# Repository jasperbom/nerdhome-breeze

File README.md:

# Nerdhome Breeze

Lokale wifi-adapters voor airco's, met ESPHome in Home Assistant. Geen cloud, geen app: het printje gaat op de service- of wifi-aansluiting van de binnenunit en praat rechtstreeks met de airco.

| Variant | Aansluiting | Print | Firmware |
|---|---|---|---|
| **Breeze voor Toshiba** | CN22 (wifi-poort, 5 V, 9600 8E1) | [`toshiba/`](toshiba/README.md), 24 × 34 mm | [`esphome/breeze-toshiba.yaml`](esphome/breeze-toshiba.yaml) |
| **Breeze voor Daikin** | S21 (12–15 V, 2400 8E2) | [`daikin/`](daikin/README.md), 28 × 42 mm | [`esphome/breeze-daikin.yaml`](esphome/breeze-daikin.yaml) |

Beide printjes gebruiken een ESP32-C6-MINI-1U (wifi 6, U.FL-antenne), USB-C voor de eerste keer flashen en MOSFET-niveau-omzetters naar de 5 V-logica van de airco.

**Status:** beide printjes zijn revisie 1.0 en nog niet in hardware getest.

## Firmware

De ESPHome-config staat in [`esphome/`](esphome/) en wordt op twee manieren gebruikt.

**1. Eigen config per binnenunit (voor ESPHome-gebruikers)**
`breeze-<merk>.yaml` bevat alles wat voor elke unit van dat merk gelijk is. Elke unit krijgt in de ESPHome Builder een kleine eigen yaml (voorbeelden: [`toshiba-woonkamer.yaml`](esphome/toshiba-woonkamer.yaml), [`daikin-voorbeeld.yaml`](esphome/daikin-voorbeeld.yaml)) met alleen naam, API-sleutel en wifi. De rest komt via `packages:` van GitHub (`refresh: 1d`).

1. Zet de waarden uit [`esphome/secrets.yaml.example`](esphome/secrets.yaml.example) in de `secrets.yaml` van de ESPHome Builder, met per unit een eigen API-sleutel (`openssl rand -base64 32`).
2. Maak per unit een kopie van het voorbeeld en pas `name`, `friendly_name` en de naam van de API-sleutel aan.
3. Eerste keer via USB-C flashen (deksel eraf, print los van de airco; niet herkend? houd BOOT ingedrukt bij het insteken). Daarna gaan updates via wifi.

**2. Kant-en-klare firmware (voor klanten, zonder compileren)**
GitHub Actions bouwt `breeze-<merk>.factory.yaml` bij elke wijziging in `esphome/` en elke 1e van de maand met de nieuwste ESPHome, en publiceert op GitHub Pages:

- Webinstaller: https://jasperbom.github.io/nerdhome-breeze/ (Chrome/Edge, via USB, wifi meteen instellen via Improv)
- Update-kanalen: `…/firmware/toshiba/manifest.json` en `…/firmware/daikin/manifest.json`

Units met deze firmware krijgen in Home Assistant een update-entiteit *Firmware*; elke nieuwe build verschijnt daar als update. Met *Take control* in de ESPHome Builder stap je over op route 1.

### Wat Breeze voor Toshiba in Home Assistant zet

- Het airco-entity (standen, temperatuur, ventilator, zwenken verticaal én horizontaal) en het vermogensniveau.
- **Actie**: of de unit echt koelt, verwarmt, ontvochtigt, ventileert of stilstaat (*inactief*), op basis van de compressor in het buitendeel.
- **Presets**: Eco, Boost (Hi POWER), Silent 1 en 2, Slapen, Comfort, Fireplace 1 en 2. Vorstbeveiliging (8 °C) en de vloerstand staan bewust uit.
- **Lamellen verticaal**: vaste stand (boven t/m onder) of zwenken.
- **Plasmafilter** aan/uit. Heeft de binnenunit geen plasmafilter, dan meldt hij nooit een stand en blijft de schakelaar op *Onbekend*.
- **Zelfreiniging**: aan zolang de unit zich na koelen of drogen droogblaast (ca. 30 minuten, ventilator laag, airco staat op uit).
- **Wifi-lampje** op de binnenunit aan/uit; de stand wordt onthouden.
- **Ruimtetemperatuur**: de unit meldt hele graden, elke minuut opgevraagd en afgevlakt met een glijdend gemiddelde over 10 minuten.
- **Buitentemperatuur** van de buitenunit (alleen als het buitendeel aan staat).
- **Energie vandaag** (kWh) uit de eigen meter van de unit en een geschat **Vermogen** (W), op modellen met energiemeting. De unit krijgt daarvoor de klok van Home Assistant.
- **Draaiuren** (totaal) en **Draaiuren sinds onderhoud**, met een instelbaar **Onderhoudsinterval** (standaard 250 uur), een melding **Onderhoud nodig** en een knop **Onderhoud uitgevoerd** die de teller op nul zet. Een uur telt mee zodra de unit aan staat, in elke stand.
- **Diagnose, standaard verborgen**: compressorbelasting en -stroom, pers- en zuiggastemperatuur, warmtewisselaar buiten en binnen (TC, TCJ) en ventilatortoerental. Deze komen uit statusberichten die niet elk model stuurt; zet ze in Home Assistant aan als je unit ze levert.
- **Typenummer, serienummer en softwareversie** van binnen- en buitendeel, zoals de unit ze zelf doorgeeft (handig bij support en garantie).
- **Van de Breeze zelf**: chiptemperatuur, IP-adres, wifi-netwerk, wifi-signaal, ESPHome-versie en uptime.

Wat een unit niet ondersteunt (bijvoorbeeld horizontale lamellen of een preset), negeert hij. Losse ESPHome-entiteiten kunnen in Home Assistant niet op *Niet beschikbaar* staan; dat kan alleen het hele apparaat.

## Licenties

De firmware gebruikt de ESPHome-componenten [esphome_toshiba_suzumi](https://github.com/pedobry/esphome_toshiba_suzumi) en [esphome-daikin-s21](https://github.com/asund/esphome-daikin-s21), beide GPL-3. Wie gecompileerde firmware verspreidt, moet de broncode beschikbaar stellen; dat gebeurt hier: de config staat in deze repository en de componenten worden bij het bouwen van GitHub gehaald. De Toshiba-component staat als aangepaste kopie (met plasmafilter) in [`esphome/components/toshiba_suzumi/`](esphome/components/toshiba_suzumi/NERDHOME.md), met de oorspronkelijke GPL-3-licentie en een overzicht van de wijzigingen. Merknamen worden alleen beschrijvend gebruikt ("voor Toshiba", "voor Daikin"); dit product is niet van of goedgekeurd door Toshiba of Daikin.

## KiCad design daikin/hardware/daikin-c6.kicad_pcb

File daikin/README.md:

# Breeze voor Daikin: print `daikin-c6`

Onderdeel van [Nerdhome Breeze](../README.md). Firmware: [`esphome/breeze-daikin.yaml`](../esphome/breeze-daikin.yaml).

Printje van 28 × 42 mm voor de **S21-aansluiting** van Daikin-binnenunits (Emura, Perfera, Stylish, Sensira, Comfora en andere huishoudelijke splitunits). Het zet de unit lokaal via ESPHome in Home Assistant, met het component [esphome-daikin-s21](https://github.com/asund/esphome-daikin-s21) (UART 2400 baud, 8E2). Commerciële systemen met P1/P2 (Sky Air, VRV, Altherma) vallen hier niet onder.

**Status: revisie 1.0, nog niet in hardware getest.** ERC en DRC (met schema-pariteit) zijn schoon en de footprints zijn uitgelijnd tegen JLCPCB's eigen footprints. Test eerst één bordje op één unit.

## Verschil met de Toshiba-print

Zelfde basis: ESP32-C6-MINI-1U met U.FL-antenne, AP2112K 3,3 V-regelaar, Schottky-OR met USB-C, twee AO3400A-niveau-omzetters, BOOT-knop en status-LED, dezelfde GPIO's (19 = TX, 20 = RX, 23 = LED).

| | Toshiba (`toshiba-c6`) | Daikin (`daikin-c6`) |
|---|---|---|
| Aansluiting | CN22, JST PA 2,0 mm | S21, JST EH 2,5 mm (S5B-EH, zijingang) |
| Voeding uit de airco | 5 V | 12–15 V op pin 4 → buck-converter AP63205 → 5 V |
| Pull-ups datalijnen | op de 5 V van de airco | op de eigen 5 V van de buck (Daikin-lijnen zijn open drain) |
| UART | 9600 8E1 | 2400 8E2 |
| Afmeting | 24 × 34 mm | 28 × 42 mm (EH-connector en USB-C passen niet samen op 24 mm) |

## Aansluiting J1 (Daikin S21)

| Pin | Functie | Op de print |
|---|---|---|
| 1 | Vref 5 V (referentie, soms afwezig) | **niet aangesloten** |
| 2 | TX van de airco | ESP RX (GPIO20) via Q2 |
| 3 | RX van de airco | ESP TX (GPIO19) via Q1 |
| 4 | Vcc 12–15 V | voeding via buck U3 |
| 5 | GND | GND |

Kabel: EHR-5 aan beide kanten, pin 1 op pin 1 (1-op-1). Sommige units hebben een JST PAP-aansluiting (2,0 mm) in plaats van EH; dan heb je een PAP-naar-EH-kabel nodig. Meet vóór het insteken pin 4 tegen pin 5: daar hoort 12–15 V te staan.

## Bestellen bij JLCPCB

Zoals bij de Toshiba-print: upload `production/daikin-c6_gerbers_jlcpcb.zip` (2 lagen, 1,6 mm), zet PCB Assembly aan voor de bovenkant en upload `production/daikin-c6_bom_jlcpcb.csv` en `production/daikin-c6_cpl_jlcpcb.csv`. Controleer in de plaatsingsvoorbeeldweergave vooral U3 (buck), U2, Q1/Q2, D1/D2 (streep = kathode), D3 en de richting van J1 (opening naar de onderrand).

Extended parts: U1, U2, U3 (AP63205WU-7), L1 (4,7 µH), J1 (S5B-EH), J2 en SW1.

## Veiligheid

- Sluit nooit USB aan terwijl het bordje aan de airco hangt.
- Werk alleen aan de binnenunit met de stroom eraf.
- Gebruik nooit de S403-aansluiting met pin 10: daar staat ongeveer 327 V DC op.

## Bestanden en opnieuw genereren

Zelfde opbouw als `toshiba/`: `hardware/` (KiCad 9), `production/` (JLCPCB), `docs/` (schema-PDF, assemblagetekening, renders), `tools/` (generatoren; `tools/circuit.py` is de enige bron voor onderdelen en netten, `tools/build_pcb.sh` en `tools/gen_outputs.sh` bouwen alles opnieuw).

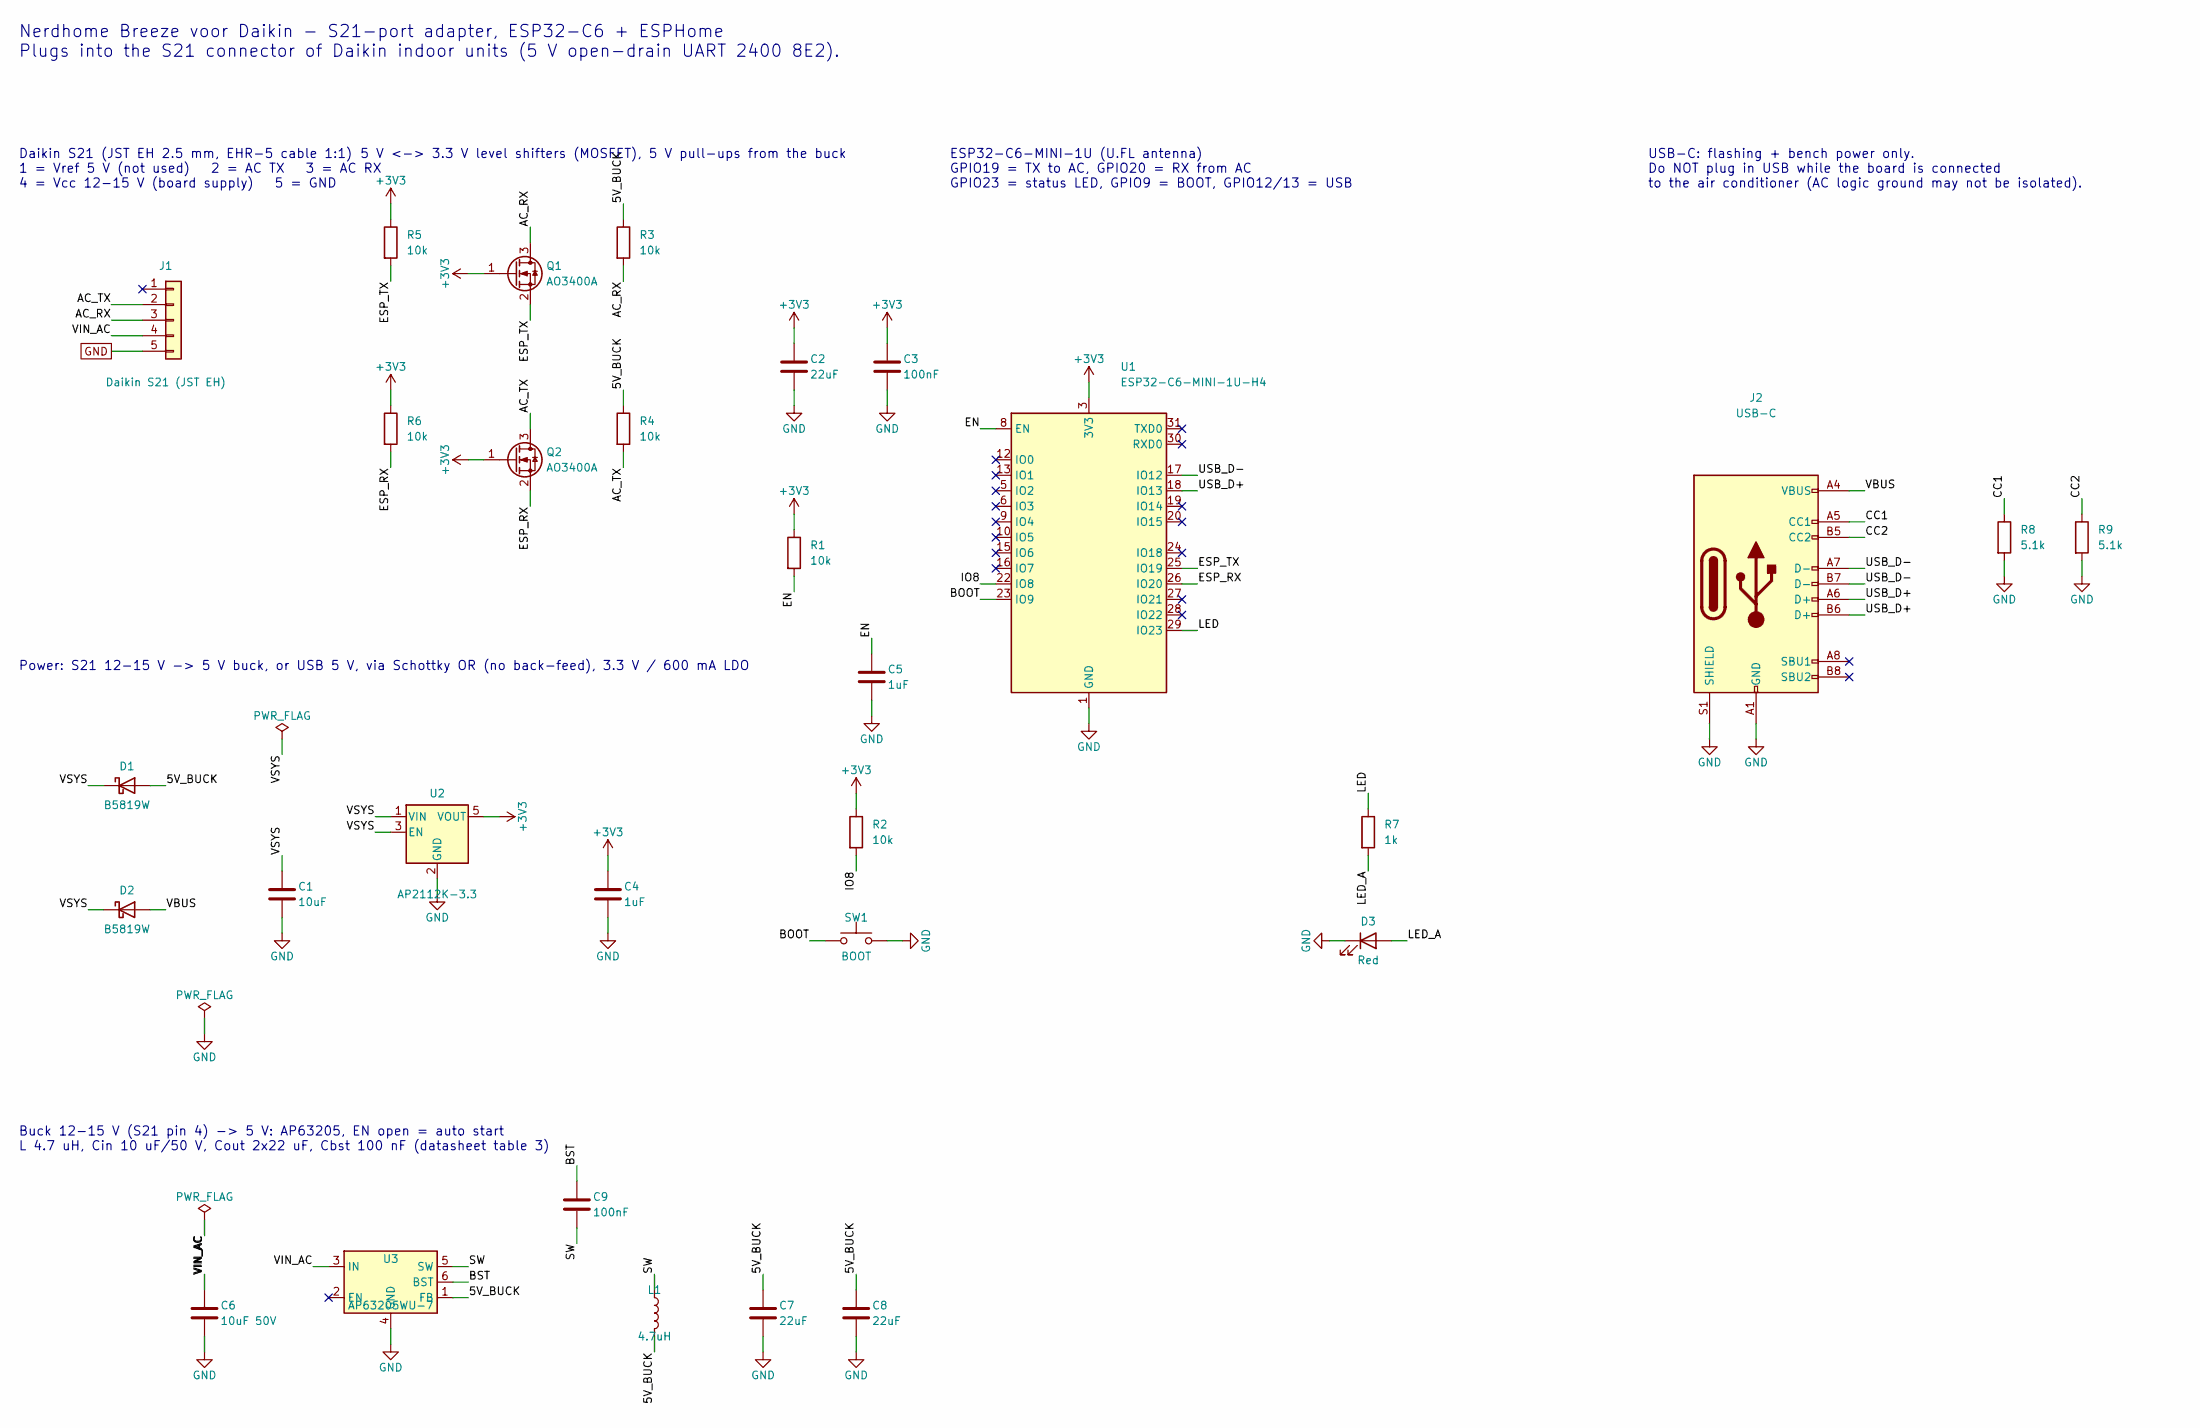
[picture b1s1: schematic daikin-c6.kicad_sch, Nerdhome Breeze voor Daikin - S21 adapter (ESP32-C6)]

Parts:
C1: 10uF; C_0603_1608Metric; MPN CL10A106KP8NNNC; LCSC C19702
C2, C7, C8: 22uF; C_0805_2012Metric; MPN CL21A226MAQNNNE; LCSC C45783
C3, C9: 100nF; C_0402_1005Metric; MPN CL05B104KO5NNNC; LCSC C1525
C4, C5: 1uF; C_0402_1005Metric; MPN CL05A105KA5NQNC; LCSC C52923
C6: 10uF 50V; C_1206_3216Metric; MPN CL31A106KBHNNNE; LCSC C13585
D1, D2: B5819W; D_SOD-123; MPN B5819W SL; LCSC C8598
D3: Red; LED_0603_1608Metric; MPN KT-0603R; LCSC C2286
J1: Daikin S21 (JST EH); JST_EH_S5B-EH_1x05_P2.50mm_Horizontal; MPN S5B-EH(LF)(SN); LCSC C265103
J2: USB-C; USB_C_Receptacle_HRO_TYPE-C-31-M-12; MPN TYPE-C-31-M-12; LCSC C165948
L1: 4.7uH; L_Cenker_CKCS4030; MPN CKCS4030-4.7uH/M; LCSC C354587
Q1, Q2: AO3400A; SOT-23; MPN AO3400A; LCSC C20917
R1, R2, R3, R4, R5, R6: 10k; R_0402_1005Metric; MPN 0402WGF1002TCE; LCSC C25744
R7: 1k; R_0402_1005Metric; MPN 0402WGF1001TCE; LCSC C11702
R8, R9: 5.1k; R_0402_1005Metric; MPN 0402WGF5101TCE; LCSC C25905
SW1: BOOT; SW_SPST_TS-1088-xR020; MPN TS-1088R-02026; LCSC C455280
U1: ESP32-C6-MINI-1U-H4; ESP32-C6-MINI-1U; MPN ESP32-C6-MINI-1U-H4; LCSC C20627095
U2: AP2112K-3.3; SOT-23-5; MPN AP2112K-3.3TRG1; LCSC C51118
U3: AP63205WU-7; TSOT-23-6; MPN AP63205WU-7; LCSC C2071056

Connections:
+3V3: C2.1, C3.1, C4.1, Q1.1 (G), Q2.1 (G), R1.1, R2.1, R5.1, R6.1, U1.3 (3V3), U2.5 (VOUT)
/5V_BUCK: C7.1, C8.1, D1.2 (A), L1.2, R3.1, R4.1, U3.1 (FB)
/AC_RX: J1.3, Q1.3 (D), R3.2
/AC_TX: J1.2, Q2.3 (D), R4.2
/BOOT: SW1.1, U1.23 (IO9)
/BST: C9.1, U3.6 (BST)
/CC1: J2.A5 (CC1), R8.1
/CC2: J2.B5 (CC2), R9.1
/EN: C5.1, R1.2, U1.8 (EN)
/ESP_RX: Q2.2 (S), R6.2, U1.26 (IO20)
/ESP_TX: Q1.2 (S), R5.2, U1.25 (IO19)
/IO8: R2.2, U1.22 (IO8)
/LED: R7.1, U1.29 (IO23)
/LED_A: D3.2 (A), R7.2
/SW: C9.2, L1.1, U3.5 (SW)
/USB_D+: J2.A6 (D+), J2.B6 (D+), U1.18 (IO13)
/USB_D-: J2.A7 (D-), J2.B7 (D-), U1.17 (IO12)
/VBUS: D2.2 (A), J2.A4 (VBUS), J2.A9 (VBUS), J2.B4 (VBUS), J2.B9 (VBUS)
/VIN_AC: C6.1, J1.4, U3.3 (IN)
/VSYS: C1.1, D1.1 (K), D2.1 (K), U2.1 (VIN), U2.3 (EN)
GND: C1.2, C2.2, C3.2, C4.2, C5.2, C6.2, C7.2, C8.2, D3.1 (K), J1.5, J2.A1 (GND), J2.A12 (GND), J2.B1 (GND), J2.B12 (GND), J2.S1 (SHIELD), R8.2, R9.2, SW1.2, U1.1 (GND), U1.2 (GND), U1.11 (GND), U1.14 (GND), U1.36 (GND), U1.37 (GND), U1.38 (GND), U1.39 (GND), U1.40 (GND), U1.41 (GND), U1.42 (GND), U1.43 (GND), U1.44 (GND), U1.45 (GND), U1.46 (GND), U1.47 (GND), U1.48 (GND), U1.49 (GND), U1.50 (GND), U1.51 (GND), U1.52 (GND), U1.53 (GND), U2.2 (GND), U3.4 (GND)

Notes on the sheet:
Nerdhome Breeze voor Daikin - S21-port adapter, ESP32-C6 + ESPHome Plugs into the S21 connector of Daikin indoor units (5 V open-drain UART 2400 8E2).
Daikin S21 (JST EH 2.5 mm, EHR-5 cable 1:1) 1 = Vref 5 V (not used) 2 = AC TX 3 = AC RX 4 = Vcc 12-15 V (board supply) 5 = GND
5 V <-> 3.3 V level shifters (MOSFET), 5 V pull-ups from the buck
Power: S21 12-15 V -> 5 V buck, or USB 5 V, via Schottky OR (no back-feed), 3.3 V / 600 mA LDO
Buck 12-15 V (S21 pin 4) -> 5 V: AP63205, EN open = auto start L 4.7 uH, Cin 10 uF/50 V, Cout 2x22 uF, Cbst 100 nF (datasheet table 3)
ESP32-C6-MINI-1U (U.FL antenna) GPIO19 = TX to AC, GPIO20 = RX from AC GPIO23 = status LED, GPIO9 = BOOT, GPIO12/13 = USB
USB-C: flashing + bench power only. Do NOT plug in USB while the board is connected to the air conditioner (AC logic ground may not be isolated).

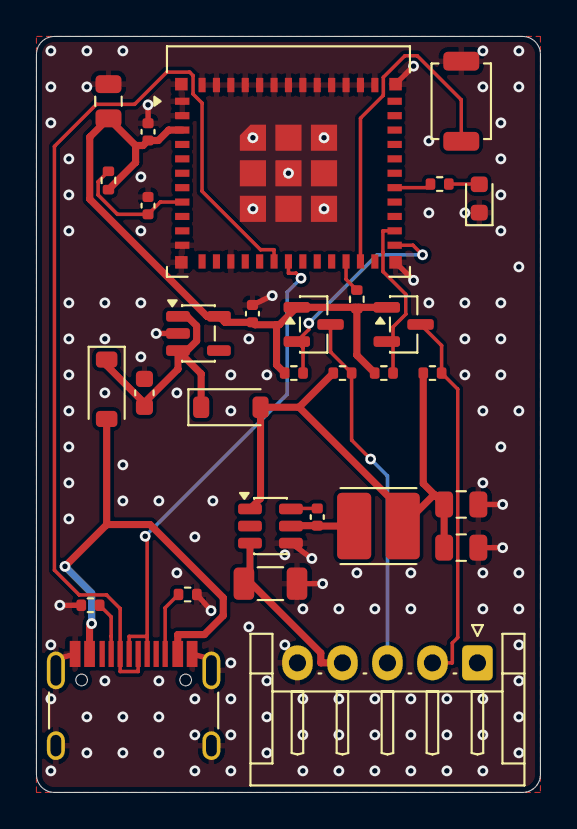
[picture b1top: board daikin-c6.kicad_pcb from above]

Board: 2 copper layers, 28.0 x 42.0 mm, 30 parts (0 on the bottom side), 21 nets.

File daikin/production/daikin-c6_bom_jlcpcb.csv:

Comment,Designator,Footprint,LCSC Part #,Quantity,MPN
10uF,C1,C_0603_1608Metric,C19702,1,CL10A106KP8NNNC
22uF,"C2,C7,C8",C_0805_2012Metric,C45783,3,CL21A226MAQNNNE
100nF,"C3,C9",C_0402_1005Metric,C1525,2,CL05B104KO5NNNC
1uF,"C4,C5",C_0402_1005Metric,C52923,2,CL05A105KA5NQNC
10uF 50V,C6,C_1206_3216Metric,C13585,1,CL31A106KBHNNNE
B5819W,"D1,D2",D_SOD-123,C8598,2,B5819W SL
Red,D3,LED_0603_1608Metric,C2286,1,KT-0603R
Daikin S21 (JST EH),J1,JST_EH_S5B-EH_1x05_P2.50mm_Horizontal,C265103,1,S5B-EH(LF)(SN)
USB-C,J2,USB_C_Receptacle_HRO_TYPE-C-31-M-12,C165948,1,TYPE-C-31-M-12
4.7uH,L1,L_Cenker_CKCS4030,C354587,1,CKCS4030-4.7uH/M
AO3400A,"Q1,Q2",SOT-23,C20917,2,AO3400A
10k,"R1,R2,R3,R4,R5,R6",R_0402_1005Metric,C25744,6,0402WGF1002TCE
1k,R7,R_0402_1005Metric,C11702,1,0402WGF1001TCE
5.1k,"R8,R9",R_0402_1005Metric,C25905,2,0402WGF5101TCE
BOOT,SW1,SW_SPST_TS-1088-xR020,C455280,1,TS-1088R-02026
ESP32-C6-MINI-1U-H4,U1,ESP32-C6-MINI-1U,C20627095,1,ESP32-C6-MINI-1U-H4
AP2112K-3.3,U2,SOT-23-5,C51118,1,AP2112K-3.3TRG1
AP63205WU-7,U3,TSOT-23-6,C2071056,1,AP63205WU-7

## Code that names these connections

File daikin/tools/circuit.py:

"""Single source of truth for the daikin-c6 (Nerdhome Breeze voor Daikin) S21 adapter circuit.

Each part: ref -> dict(sym, value, fp, lcsc, mpn, pins={pin_number: net})
Pins not listed are left unconnected (and get a no-connect flag in the schematic
when they are I/O pins).
"""

PROJECT = "daikin-c6"

# Connector J1 pinout (Daikin S21, JST EH 2.5 mm, cable EHR-5 one-to-one):
#   1 Vref 5 V   = NOT connected (reference only, sometimes absent)
#   2 TX of AC   (ESP RX via level shifter, open drain, 5 V)
#   3 RX of AC   (ESP TX via level shifter, open drain, 5 V)
#   4 Vcc 12-15 V (powers the board through the AP63205 buck -> 5 V)
#   5 GND
# Data lines are pulled up to our own 5 V (R3/R4); 2400 baud 8E2.
# GPIO plan (ESP32-C6-MINI-1U):
#   GPIO19 (pin 25) = UART TX to AC, GPIO20 (pin 26) = UART RX from AC
#   GPIO23 (pin 29) = status LED (active high)
#   GPIO9  (pin 23) = BOOT button (strapping, internal pull-up)
#   GPIO8  (pin 22) = strapping, 10k pull-up for reliable download mode
#   GPIO12/13 (pins 17/18) = native USB D-/D+

PARTS = {
    "U1": dict(sym="RF_Module:ESP32-C6-MINI-1", value="ESP32-C6-MINI-1U-H4",
               fp="daikin-c6:ESP32-C6-MINI-1U", lcsc="C20627095", mpn="ESP32-C6-MINI-1U-H4",
               pins={"3": "+3V3", "8": "EN", "17": "USB_D-", "18": "USB_D+",
                     "22": "IO8", "23": "BOOT", "25": "ESP_TX", "26": "ESP_RX", "29": "LED",
                     **{str(p): "GND" for p in [1, 2, 11, 14] + list(range(36, 54))}}),
    "U2": dict(sym="Regulator_Linear:AP2112K-3.3", value="AP2112K-3.3",
               fp="Package_TO_SOT_SMD:SOT-23-5", lcsc="C51118", mpn="AP2112K-3.3TRG1",
               pins={"1": "VSYS", "2": "GND", "3": "VSYS", "5": "+3V3"}),
    "J1": dict(sym="Connector_Generic:Conn_01x05", value="Daikin S21 (JST EH)",
               fp="Connector_JST:JST_EH_S5B-EH_1x05_P2.50mm_Horizontal", lcsc="C265103",
               mpn="S5B-EH(LF)(SN)",
               pins={"2": "AC_TX", "3": "AC_RX", "4": "VIN_AC", "5": "GND"}),
    # 12-15 V from the S21 port -> 5 V (AP63205, 1.1 MHz, datasheet table 3: 4.7 uH, 10 uF, 2x22 uF, 100 nF)
    "U3": dict(sym="Regulator_Switching:AP63205WU", value="AP63205WU-7",
               fp="Package_TO_SOT_SMD:TSOT-23-6", lcsc="C2071056", mpn="AP63205WU-7",
               pins={"1": "5V_BUCK", "3": "VIN_AC", "4": "GND", "5": "SW", "6": "BST"}),
    "L1": dict(sym="Device:L", value="4.7uH", fp="Inductor_SMD:L_Cenker_CKCS4030", lcsc="C354587",
               mpn="CKCS4030-4.7uH/M", pins={"1": "SW", "2": "5V_BUCK"}),
    "C6": dict(sym="Device:C", value="10uF 50V", fp="Capacitor_SMD:C_1206_3216Metric", lcsc="C13585",
               mpn="CL31A106KBHNNNE", pins={"1": "VIN_AC", "2": "GND"}),
    "C7": dict(sym="Device:C", value="22uF", fp="Capacitor_SMD:C_0805_2012Metric", lcsc="C45783",
               mpn="CL21A226MAQNNNE", pins={"1": "5V_BUCK", "2": "GND"}),
    "C8": dict(sym="Device:C", value="22uF", fp="Capacitor_SMD:C_0805_2012Metric", lcsc="C45783",
               mpn="CL21A226MAQNNNE", pins={"1": "5V_BUCK", "2": "GND"}),
    "C9": dict(sym="Device:C", value="100nF", fp="Capacitor_SMD:C_0402_1005Metric", lcsc="C1525",
               mpn="CL05B104KO5NNNC", pins={"1": "BST", "2": "SW"}),
    "J2": dict(sym="Connector:USB_C_Receptacle_USB2.0_16P", value="USB-C",
               fp="Connector_USB:USB_C_Receptacle_HRO_TYPE-C-31-M-12", lcsc="C165948",
               mpn="TYPE-C-31-M-12",
               pins={"A1": "GND", "A12": "GND", "B1": "GND", "B12": "GND", "S1": "GND",
                     "A4": "VBUS", "A9": "VBUS", "B4": "VBUS", "B9": "VBUS",
                     "A5": "CC1", "B5": "CC2",
                     "A6": "USB_D+", "B6": "USB_D+", "A7": "USB_D-", "B7": "USB_D-"}),
    "D1": dict(sym="Device:D_Schottky", value="B5819W",
               fp="Diode_SMD:D_SOD-123", lcsc="C8598", mpn="B5819W SL",
               pins={"1": "VSYS", "2": "5V_BUCK"}),
    "D2": dict(sym="Device:D_Schottky", value="B5819W",
               fp="Diode_SMD:D_SOD-123", lcsc="C8598", mpn="B5819W SL",
               pins={"1": "VSYS", "2": "VBUS"}),
    "D3": dict(sym="Device:LED", value="Red",
               fp="LED_SMD:LED_0603_1608Metric", lcsc="C2286", mpn="KT-0603R",
               pins={"1": "GND", "2": "LED_A"}),
    "Q1": dict(sym="Transistor_FET:AO3400A", value="AO3400A",
               fp="Package_TO_SOT_SMD:SOT-23", lcsc="C20917", mpn="AO3400A",
               pins={"1": "+3V3", "2": "ESP_TX", "3": "AC_RX"}),
    "Q2": dict(sym="Transistor_FET:AO3400A", value="AO3400A",
               fp="Package_TO_SOT_SMD:SOT-23", lcsc="C20917", mpn="AO3400A",
               pins={"1": "+3V3", "2": "ESP_RX", "3": "AC_TX"}),
    "SW1": dict(sym="Switch:SW_Push", value="BOOT",
                fp="Button_Switch_SMD:SW_SPST_TS-1088-xR020", lcsc="C455280", mpn="TS-1088R-02026",
                pins={"1": "BOOT", "2": "GND"}),
    "R1": dict(sym="Device:R", value="10k", fp="Resistor_SMD:R_0402_1005Metric", lcsc="C25744",
               mpn="0402WGF1002TCE", pins={"1": "+3V3", "2": "EN"}),
    "R2": dict(sym="Device:R", value="10k", fp="Resistor_SMD:R_0402_1005Metric", lcsc="C25744",
               mpn="0402WGF1002TCE", pins={"1": "+3V3", "2": "IO8"}),
    "R3": dict(sym="Device:R", value="10k", fp="Resistor_SMD:R_0402_1005Metric", lcsc="C25744",
               mpn="0402WGF1002TCE", pins={"1": "5V_BUCK", "2": "AC_RX"}),
    "R4": dict(sym="Device:R", value="10k", fp="Resistor_SMD:R_0402_1005Metric", lcsc="C25744",
               mpn="0402WGF1002TCE", pins={"1": "5V_BUCK", "2": "AC_TX"}),
    "R5": dict(sym="Device:R", value="10k", fp="Resistor_SMD:R_0402_1005Metric", lcsc="C25744",
               mpn="0402WGF1002TCE", pins={"1": "+3V3", "2": "ESP_TX"}),
    "R6": dict(sym="Device:R", value="10k", fp="Resistor_SMD:R_0402_1005Metric", lcsc="C25744",
               mpn="0402WGF1002TCE", pins={"1": "+3V3", "2": "ESP_RX"}),
    "R7": dict(sym="Device:R", value="1k", fp="Resistor_SMD:R_0402_1005Metric", lcsc="C11702",
               mpn="0402WGF1001TCE", pins={"1": "LED", "2": "LED_A"}),
    "R8": dict(sym="Device:R", value="5.1k", fp="Resistor_SMD:R_0402_1005Metric", lcsc="C25905",
               mpn="0402WGF5101TCE", pins={"1": "CC1", "2": "GND"}),
    "R9": dict(sym="Device:R", value="5.1k", fp="Resistor_SMD:R_0402_1005Metric", lcsc="C25905",
               mpn="0402WGF5101TCE", pins={"1": "CC2", "2": "GND"}),
    "C1": dict(sym="Device:C", value="10uF", fp="Capacitor_SMD:C_0603_1608Metric", lcsc="C19702",
               mpn="CL10A106KP8NNNC", pins={"1": "VSYS", "2": "GND"}),
    "C2": dict(sym="Device:C", value="22uF", fp="Capacitor_SMD:C_0805_2012Metric", lcsc="C45783",
               mpn="CL21A226MAQNNNE", pins={"1": "+3V3", "2": "GND"}),
    "C3": dict(sym="Device:C", value="100nF", fp="Capacitor_SMD:C_0402_1005Metric", lcsc="C1525",
               mpn="CL05B104KO5NNNC", pins={"1": "+3V3", "2": "GND"}),
    "C4": dict(sym="Device:C", value="1uF", fp="Capacitor_SMD:C_0402_1005Metric", lcsc="C52923",
               mpn="CL05A105KA5NQNC", pins={"1": "+3V3", "2": "GND"}),
    "C5": dict(sym="Device:C", value="1uF", fp="Capacitor_SMD:C_0402_1005Metric", lcsc="C52923",
               mpn="CL05A105KA5NQNC", pins={"1": "EN", "2": "GND"}),
}

POWER_NETS = {"VSYS", "5V_BUCK", "VIN_AC", "VBUS", "+3V3", "GND"}


def nets():
    out = {}
    for ref, p in PARTS.items():
        for pin, net in p["pins"].items():
            out.setdefault(net, []).append((ref, pin))
    return out


if __name__ == "__main__":
    for n, nodes in sorted(nets().items()):
        print(n, len(nodes), nodes if len(nodes) < 12 else str(len(nodes)) + " nodes")
